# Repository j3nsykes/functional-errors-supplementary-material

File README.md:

# functional-errors-supplementary-material

This repo contains supplementary material for a PhD thesis.

## Contents

### Feedback Shield
This directory contains the Arduino code that drives the Feedback Shield. Each iteration can be accessed alongside testing code and future experiments.

### Feedback Shield Schematics
The latest schematic and board designs for the Feedback Shield can be located here. This is iteration two's designs.

### Results
The raw data, cleaned tables, statistical analysis and survey imagery can be accessed here.

### Sculpting Code
This is the code for the sculpting code web application. It is the latest version but older commits and versions can be located in the original [repo](https://github.com/j3nsykes/sculpting-code)

### Study Learning Resources
The custom websites built for the studies can be located here and run locally if required.

### Video Links
Video documentation of the Sculpting Code iterations are on Vimeo. The links to which are stored here.

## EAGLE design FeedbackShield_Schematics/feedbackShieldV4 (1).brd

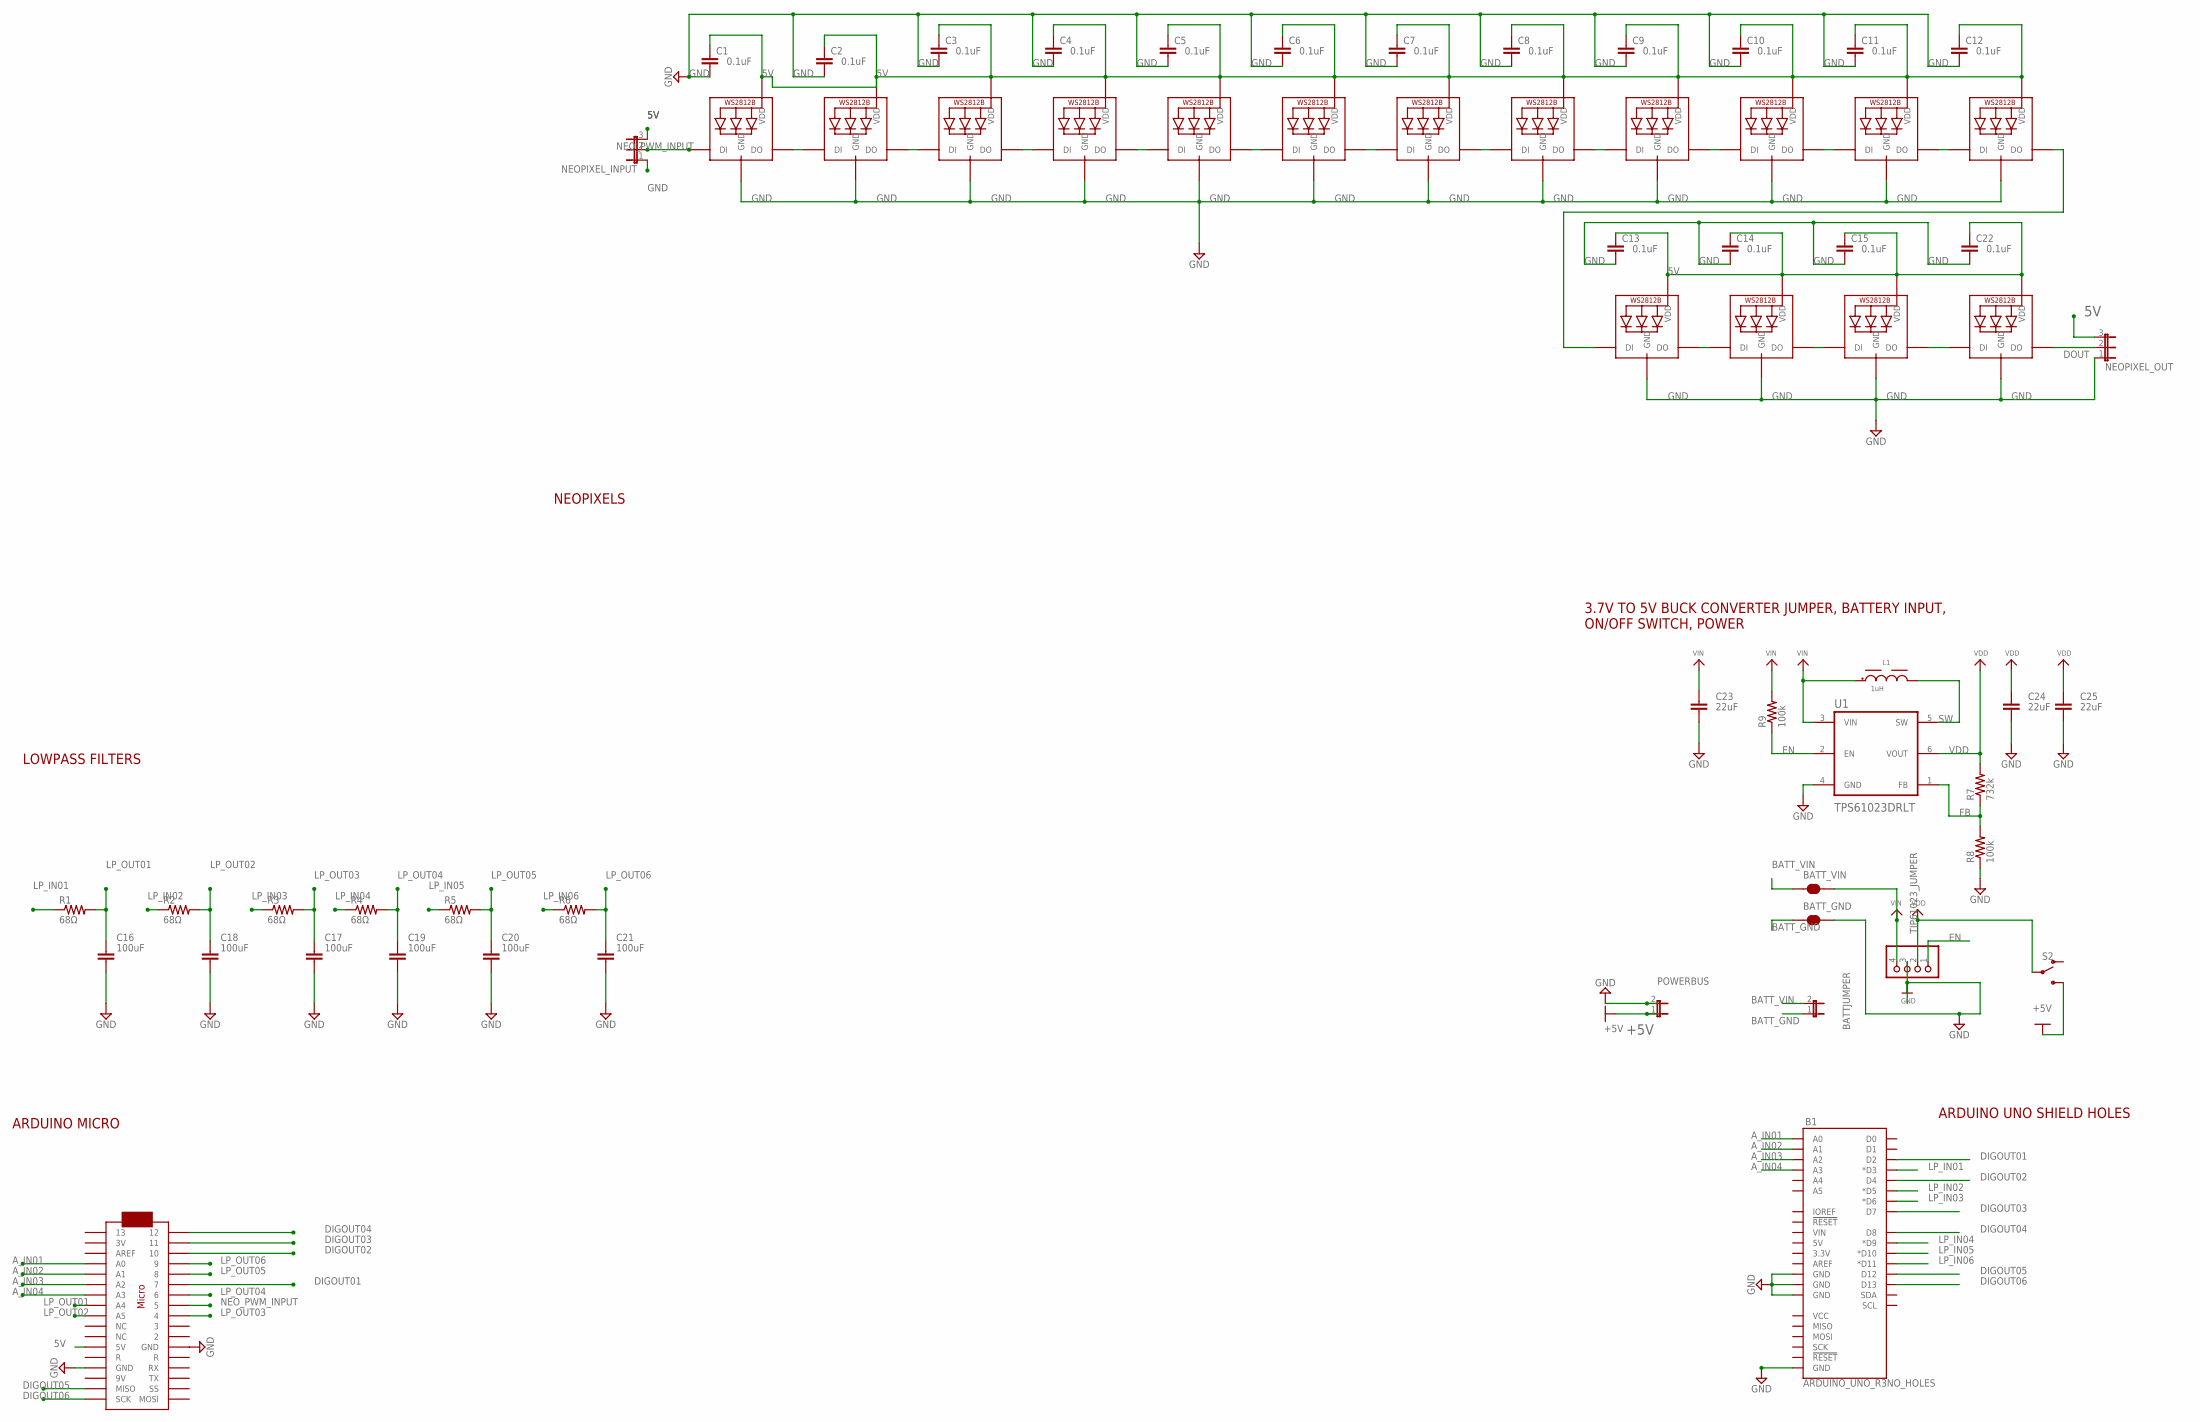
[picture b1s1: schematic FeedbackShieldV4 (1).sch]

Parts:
B1: ARDUINO_UNO_R3NO_HOLES; ARDUINO_R3_NO_HOLES
BATTJUMPER: JP1E; JP1
BATT_GND: JUMPER-SMT_2_NC_TRACE_SILK; SMT-JUMPER_2_NC_TRACE_SILK
BATT_VIN: JUMPER-SMT_2_NC_TRACE_SILK; SMT-JUMPER_2_NC_TRACE_SILK
C1, C2, C3, C4, C5, C6, C7, C8, C9, C10, C11, C12, C13, C14, C15, C22: 0.1uF; CAPC1608X85
C16, C17, C18, C19, C20, C21: 100uF; CAPC3216X135
C23, C24, C25: 22uF; CAPC2012X110
L1: 1uH; WE-MAPI_4020
MICRO: ARDUINOMICRO
NEOPIXEL_INPUT: JP2E; JP2
NEOPIXEL_OUT: JP2E; JP2
PIN2, PIN3, PIN4, PIN5, PIN6, PIN7, PIN8, PIN9, PIN10, PIN11, PIN12, PIN13: WS2812B3535; LED3535
PINA0, PINA1, PINA2, PINA3: WS2812B3535; LED3535
POWERBUS: JP1E; JP1
R1, R2, R3, R4, R5, R6: 68Ω; RESC2012X65
R7: 732k; RESC2012X65
R8, R9: 100k; RESC2012X65
S2: SWITCH-SPDT-SMD-RIGHT-ANGLE; SWITCH_SPST_SMD_A
TIP61023_JUMPER: HEADER-1X4ROUND; 1X04_ROUND
U1: TPS61023DRLT; SOT50P160X60-6N

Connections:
5V: C1.1, C2.1, C3.1, C4.1, C5.1, C6.1, C7.1, C8.1, C9.1, C10.1, C11.1, C12.1, C13.1, C14.1, C15.1, C22.1, MICRO.P$23 (5V), NEOPIXEL_INPUT.3, NEOPIXEL_OUT.3, PIN2.2 (VDD), PIN3.2 (VDD), PIN4.2 (VDD), PIN5.2 (VDD), PIN6.2 (VDD), PIN7.2 (VDD), PIN8.2 (VDD), PIN9.2 (VDD), PIN10.2 (VDD), PIN11.2 (VDD), PIN12.2 (VDD), PIN13.2 (VDD), PINA0.2 (VDD), PINA1.2 (VDD), PINA2.2 (VDD), PINA3.2 (VDD)
+5V: POWERBUS.1, S2.3 (S)
A_IN01: B1.A0, MICRO.P$31 (A0)
A_IN02: B1.A1, MICRO.P$30 (A1)
A_IN03: B1.A2, MICRO.P$29 (A2)
A_IN04: B1.A3, MICRO.P$28 (A3)
BATT_GND: BATTJUMPER.1, BATT_GND.1
BATT_VIN: BATTJUMPER.2, BATT_VIN.1
DIGOUT01: B1.D2, MICRO.P$6 (7)
DIGOUT02: B1.D4, MICRO.P$3 (10)
DIGOUT03: B1.D7, MICRO.P$2 (11)
DIGOUT04: B1.D8, MICRO.P$1 (12)
DIGOUT05: B1.D12, MICRO.P$19 (MISO)
DIGOUT06: B1.D13, MICRO.P$18 (SCK)
DOUT: NEOPIXEL_OUT.2, PINA3.3 (DO)
EN: R9.1, TIP61023_JUMPER.1, U1.2 (EN)
FB: R7.1, R8.2, U1.1 (FB)
GND: B1.GND@1 (GND), B1.GND@2 (GND), B1.GND@3 (GND), B1.GND@4 (GND), BATT_GND.2, C1.2, C2.2, C3.2, C4.2, C5.2, C6.2, C7.2, C8.2, C9.2, C10.2, C11.2, C12.2, C13.2, C14.2, C15.2, C16.2, C17.2, C18.2, C19.2, C20.2, C21.2, C22.2, C23.2, C24.2, C25.2, MICRO.P$12 (GND), MICRO.P$21 (GND), NEOPIXEL_INPUT.1, NEOPIXEL_OUT.1, PIN2.4 (GND), PIN3.4 (GND), PIN4.4 (GND), PIN5.4 (GND), PIN6.4 (GND), PIN7.4 (GND), PIN8.4 (GND), PIN9.4 (GND), PIN10.4 (GND), PIN11.4 (GND), PIN12.4 (GND), PIN13.4 (GND), PINA0.4 (GND), PINA1.4 (GND), PINA2.4 (GND), PINA3.4 (GND), POWERBUS.2, R8.1, TIP61023_JUMPER.3, U1.4 (GND)
LP_IN01: B1.D3 (*D3), R1.1
LP_IN02: B1.D5 (*D5), R2.1
LP_IN03: B1.D6 (*D6), R3.1
LP_IN04: B1.D9 (*D9), R4.1
LP_IN05: B1.D10 (*D10), R5.1
LP_IN06: B1.D11 (*D11), R6.1
LP_OUT01: C16.1, MICRO.P$27 (A4), R1.2
LP_OUT02: C18.1, MICRO.P$26 (A5), R2.2
LP_OUT03: C17.1, MICRO.P$9 (4), R3.2
LP_OUT04: C19.1, MICRO.P$7 (6), R4.2
LP_OUT05: C20.1, MICRO.P$5 (8), R5.2
LP_OUT06: C21.1, MICRO.P$4 (9), R6.2
unnamed: PINA2.3 (DO), PINA3.1 (DI)
unnamed: PIN12.3 (DO), PIN13.1 (DI)
unnamed: PIN2.3 (DO), PIN3.1 (DI)
unnamed: PIN3.3 (DO), PIN4.1 (DI)
unnamed: PIN4.3 (DO), PIN5.1 (DI)
unnamed: PIN5.3 (DO), PIN6.1 (DI)
unnamed: PIN6.3 (DO), PIN7.1 (DI)
unnamed: PIN7.3 (DO), PIN8.1 (DI)
unnamed: PIN8.3 (DO), PIN9.1 (DI)
unnamed: PIN9.3 (DO), PIN10.1 (DI)
unnamed: PIN10.3 (DO), PIN11.1 (DI)
unnamed: PIN11.3 (DO), PIN12.1 (DI)
unnamed: PIN13.3 (DO), PINA0.1 (DI)
unnamed: PINA0.3 (DO), PINA1.1 (DI)
unnamed: PINA1.3 (DO), PINA2.1 (DI)
NEO_PWM_INPUT: MICRO.P$8 (5), NEOPIXEL_INPUT.2, PIN2.1 (DI)
SW: L1.2, U1.5 (SW)
VDD: C24.1, C25.1, R7.2, S2.2, TIP61023_JUMPER.2, U1.6 (VOUT)
VIN: BATT_VIN.2, C23.1, L1.1, R9.2, TIP61023_JUMPER.4, U1.3 (VIN)

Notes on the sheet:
NEOPIXELS
LOWPASS FILTERS
ARDUINO MICRO
ARDUINO UNO SHIELD HOLES
3.7V TO 5V BUCK CONVERTER JUMPER, BATTERY INPUT, ON/OFF SWITCH, POWER

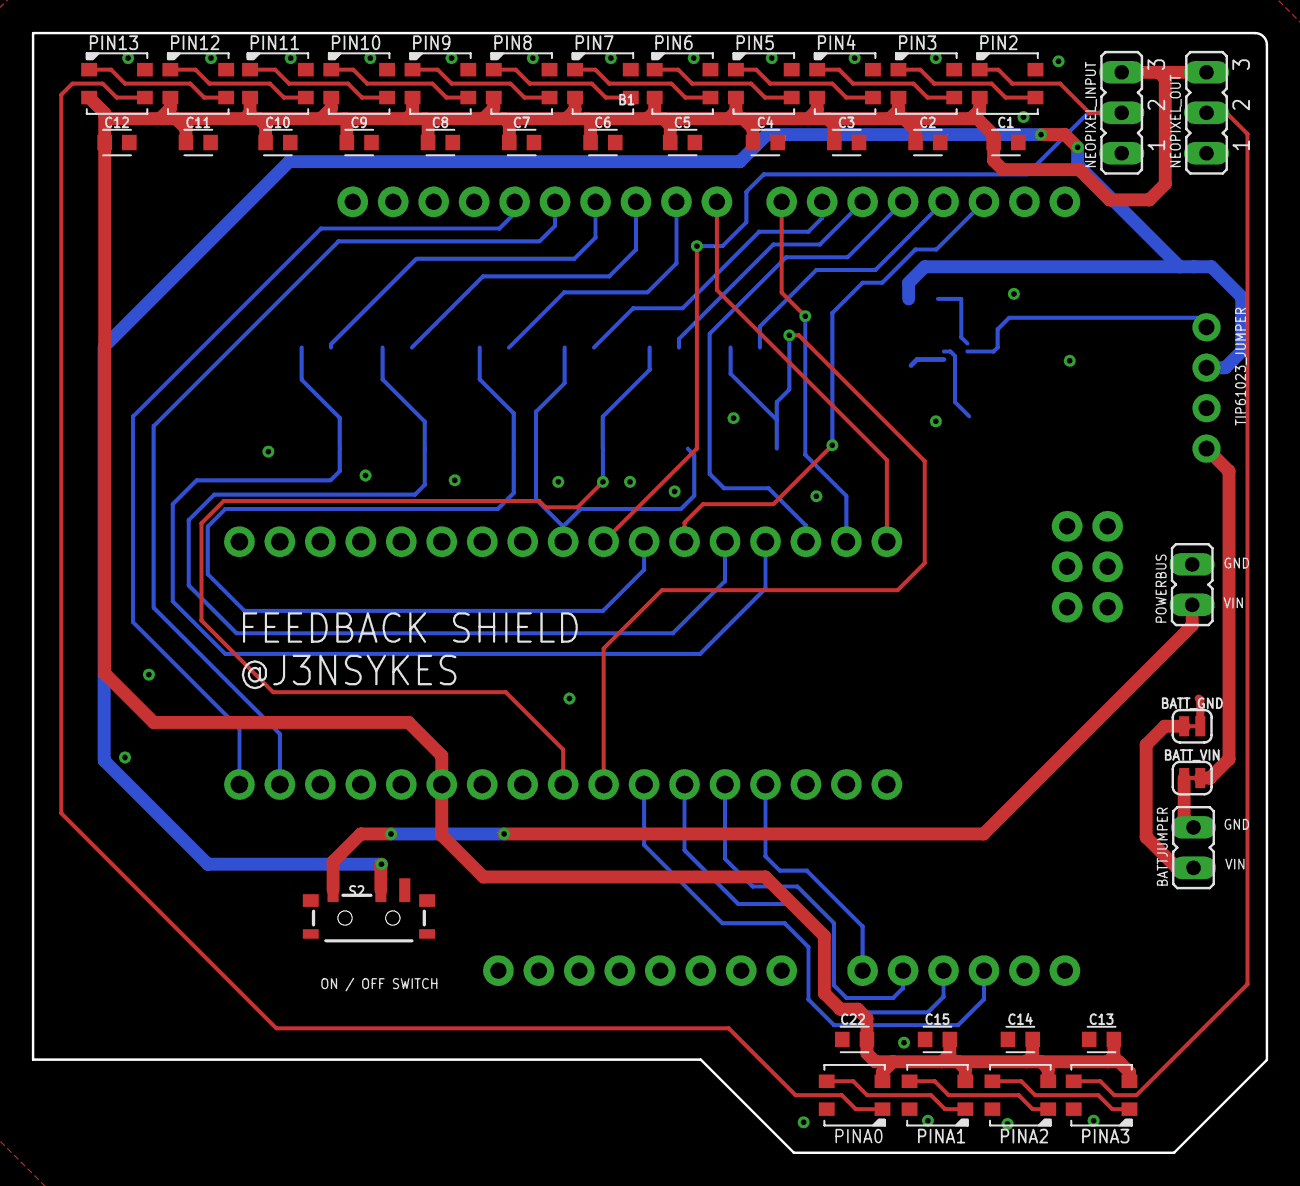
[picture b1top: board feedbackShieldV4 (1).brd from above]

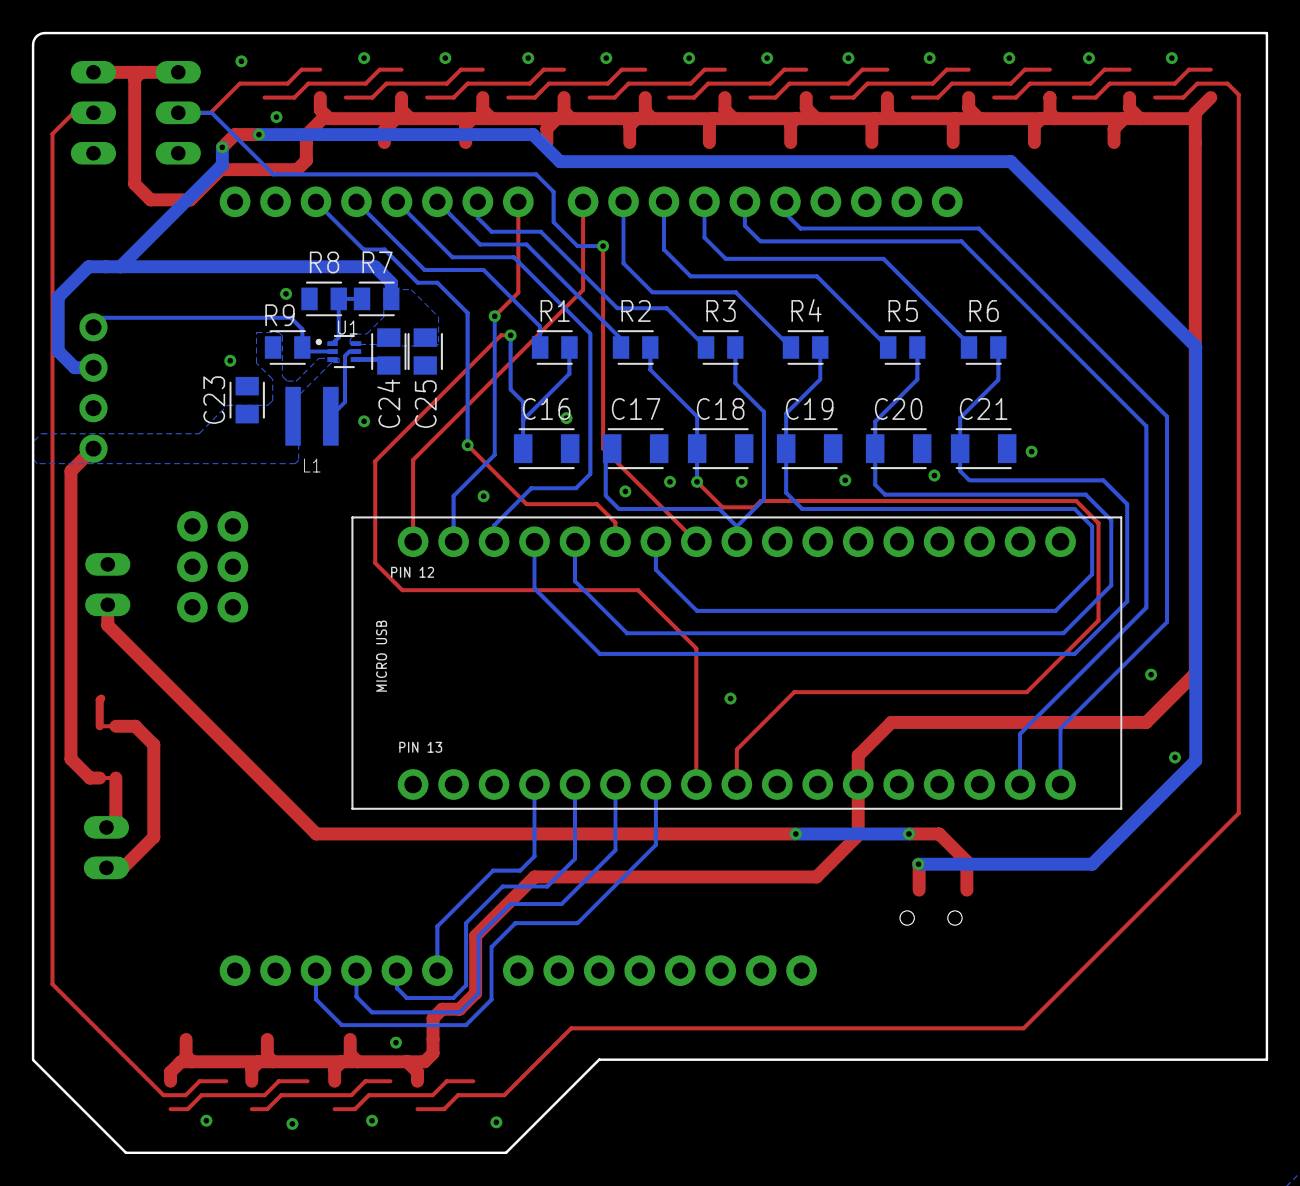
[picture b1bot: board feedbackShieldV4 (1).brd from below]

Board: 2 copper layers, 77.5 x 70.3 mm, 62 parts (21 on the bottom side), 49 nets.

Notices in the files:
parts and their libraries:
microbuilder: This work is placed in the public domain, and may be freely used for commercial and non-commercial work with the following conditions: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
Eagle_WE-MAPI: Copyright: Würth Elektronik
